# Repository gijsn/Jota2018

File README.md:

# Jota2018
Jota printje van 2018

In 2018 was het thema van de Jota 'Star Wars' waarvoor ik het volgende printje heb ontworpen

Deze R2D2 kan verschillende dingen:
* Infrarood ontvangen (draadloos communiceren)
* Connecten met een andere R2D2 (bedraad communiceren)
* Dobbelsteen (0-9)
* RGB led

Via het knopje zijn verschillende functies te selecteren

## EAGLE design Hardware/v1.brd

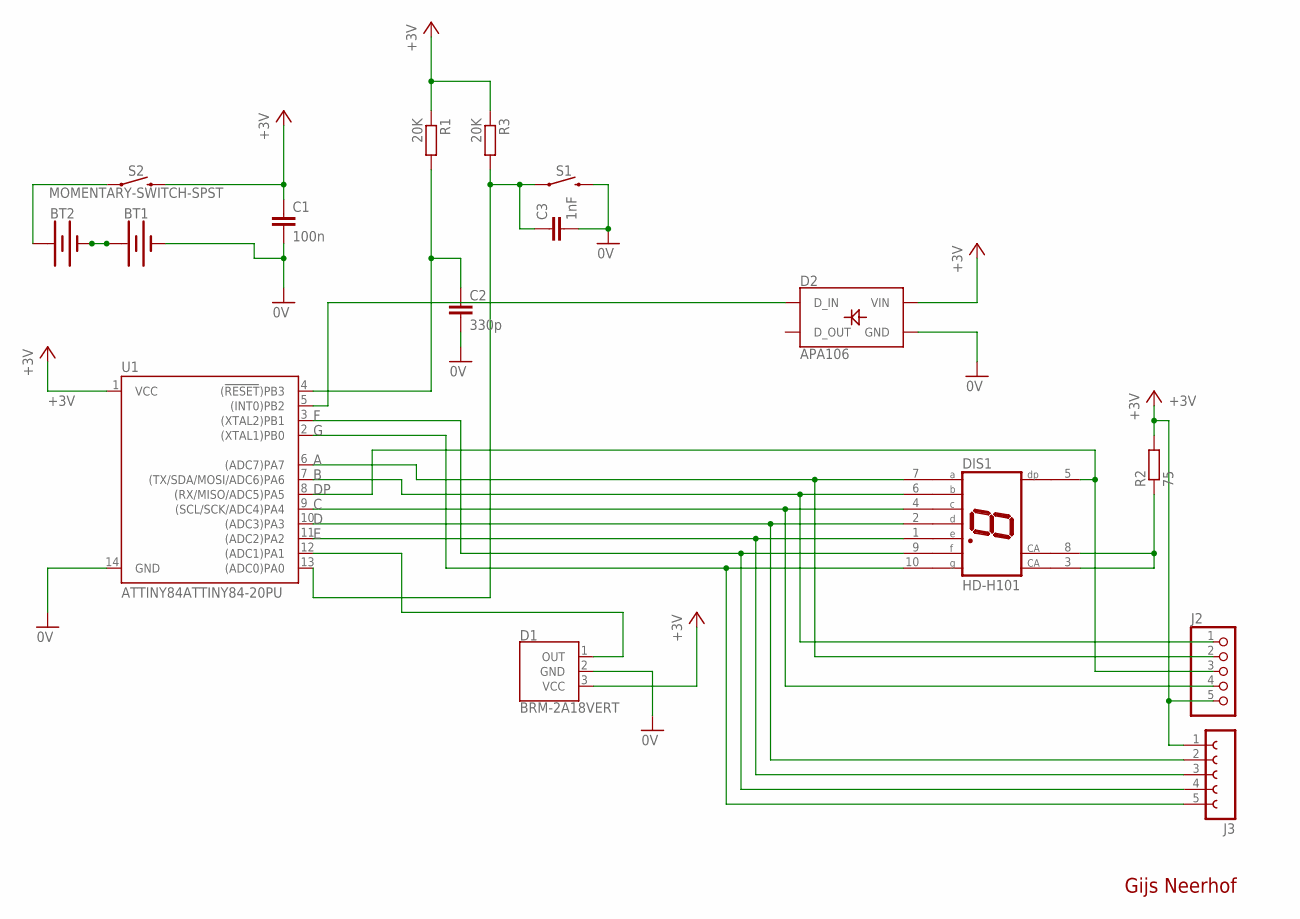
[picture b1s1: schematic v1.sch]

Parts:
BT1, BT2: BATTERY-AAA_KIT; BATTERY-AAA-KIT
C1: 100n; C050-030X075
C2: 330p; C050-030X075
C3: 1nF; C050-030X075
D1: BRM-2A18VERT; BRM-2508_VERT
D2: APA106; LED-RGB-THRU
DIS1: HD-H101; HDSP-M
J2: PINHD-1X5/90; 1X05/90
J3: FE05W
R1, R3: 20K; 0207/10
R2: 75; 0207/10
S1: MOMENTARY-SWITCH-SPST-PTH-6.0MM; TACTILE_SWITCH_PTH_6.0MM
S2: MOMENTARY-SWITCH-SPST; SAFETY_PIN_SWITCH
U1: ATTINY84ATTINY84-20PU; DIP14

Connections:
+3V: D1.3 (VCC), D2.2 (VIN), J2.5, J3.1, R1.1, R2.2, R3.1, U1.1 (VCC)
+5V: C1.1, S2.P$2 (2)
A: DIS1.7 (A), J2.2, U1.6 ((ADC7)PA7)
B: DIS1.6 (B), J2.1, U1.7 ((TX/SDA/MOSI/ADC6)PA6)
C: DIS1.4 (C), J2.4, U1.9 ((SCL/SCK/ADC4)PA4)
D: DIS1.2 (D), J3.2, U1.10 ((ADC3)PA3)
DP: DIS1.5 (DP), J2.3, U1.8 ((RX/MISO/ADC5)PA5)
E: DIS1.1 (E), J3.3, U1.11 ((ADC2)PA2)
F: DIS1.9 (F), J3.4, U1.3 ((XTAL2)PB1)
G: DIS1.10 (G), J3.5, U1.2 ((XTAL1)PB0)
GND: BT1.GND@1 (-), BT1.GND@2 (-), C1.2, C2.2, C3.2, D1.2 (GND), D2.3 (GND), S1.3 (2), U1.14 (GND)
unnamed: BT1.PWR@1 (+), BT1.PWR@2 (+), BT2.GND@1 (-), BT2.GND@2 (-)
unnamed: BT2.PWR@1 (+), BT2.PWR@2 (+), S2.P$1 (1)
unnamed: C3.1, R3.2, S1.1, U1.13 ((ADC0)PA0)
unnamed: D1.1 (OUT), U1.12 ((ADC1)PA1)
unnamed: C2.1, R1.2, U1.4 ((!RESET!)PB3)
unnamed: DIS1.3 (CA), DIS1.8 (CA), R2.1
unnamed: D2.1 (D_IN), U1.5 ((INT0)PB2)

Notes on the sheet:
Gijs Neerhof

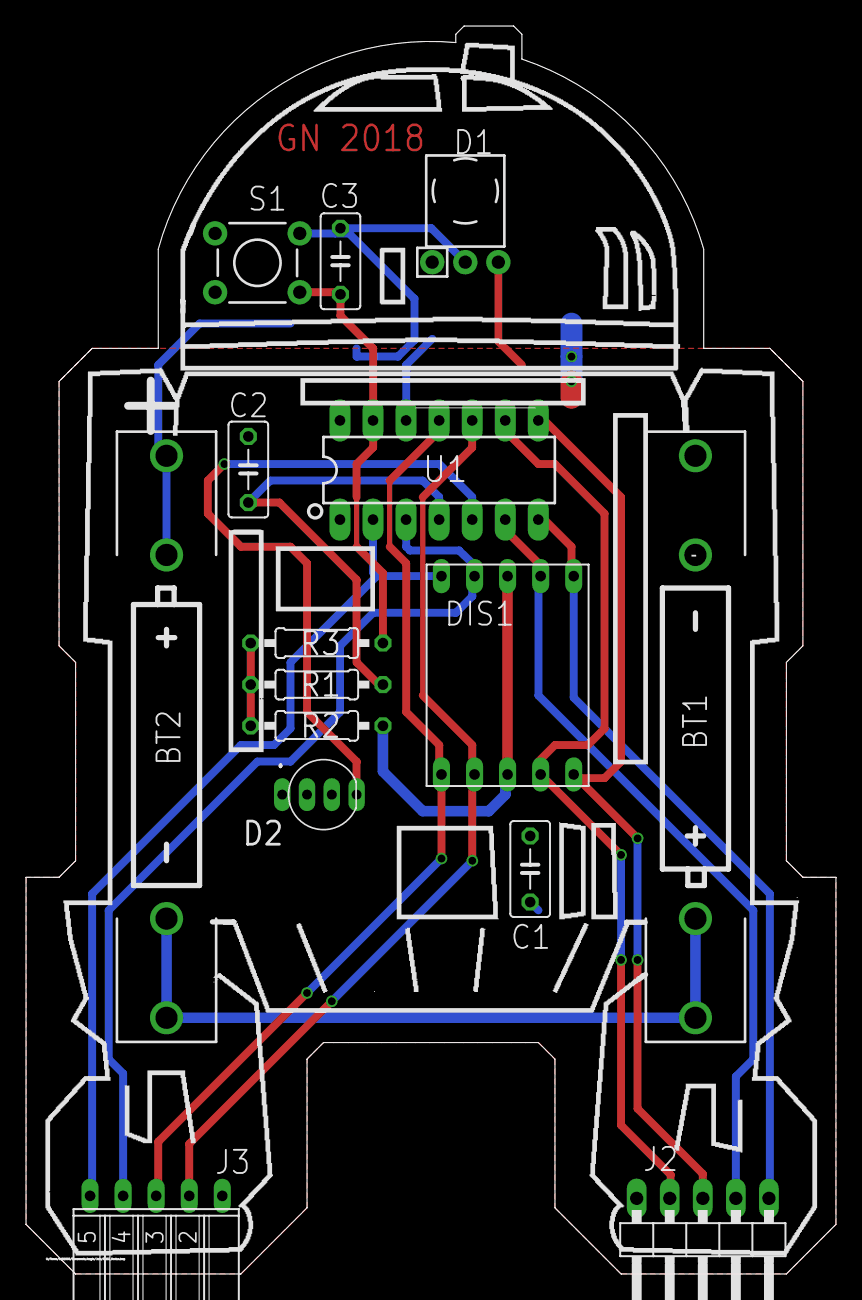
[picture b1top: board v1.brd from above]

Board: 2 copper layers, 62.2 x 95.9 mm, 17 parts (1 on the bottom side), 18 nets.

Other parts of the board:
U$1: A4L-LOC

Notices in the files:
parts and their libraries:
SparkFun-Batteries: Licensing: Creative Commons ShareAlike 4.0 International - https://creativecommons.org/licenses/by-sa/4.0
